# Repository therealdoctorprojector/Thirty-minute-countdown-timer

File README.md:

Thirty minute countdown timer.

If you have ever needed to know when half an hour has passed, this project is for you.
When you turn this device on it will:
Start a countdown timer for 30 minutes.
Show the time remaining.
After 30 minutes a speaker will make a continuous sound until you turn the device off.

The files provided should give you everything you need to make your own timer.
Note that some skill and knowledge are required to make this.

Files:
1. Software source code.
2. Bill Of Materials.
3. PCB design files.

General notes on the software:
1. The software was developed and tested using the Arduino IDE.
2. The thirty minutes has been hard-coded in the software, but you are welcome to change that number and re-compile the software.
3. You can add extra features to the software as you see fit.

General notes on the Bill Of Materials:
1. Prices on the parts are estimates only.
2. There are many variants on the OLED display, in terms of pin count, pin assignments and variations in the size and hole spacing.
3. The switch must be a mechanical latching type.

General notes on the PCB:
1. All through-hole components for ease of soldering.
2. AA batteries are the preferred power source. With some minor adjustments you could use a CR123 lithium battery, or a CR2032 lithium coin cell. You are encouraged to change the PCB design to accommodate the relevant battery holders.
3. The AA battery holder is a widely-copied design “Keystone 2462”, this should give you the correct pin-spacing to fit.
4. I don’t recommend it but you can solder the display board to the main PCB.
5. You are welcome to substitute a surface mount ATTiny85 by making the relevant changes to the PCB. I may generate a revision of the PCB which can be populated with either the 8 pin DIP or the 8-SOIC version.
6. An ICSP header is included on the PCB. No need to fit a 3x2 pin header if you use the Sparkfun PoGo adapter.
7. M3 clearance holes in each corner for fitting the PCB in an enclosure. I would encourage 3D printer users to share a simple design for a suitable case.
8. M2 clearance holes provided to support the OLED display.

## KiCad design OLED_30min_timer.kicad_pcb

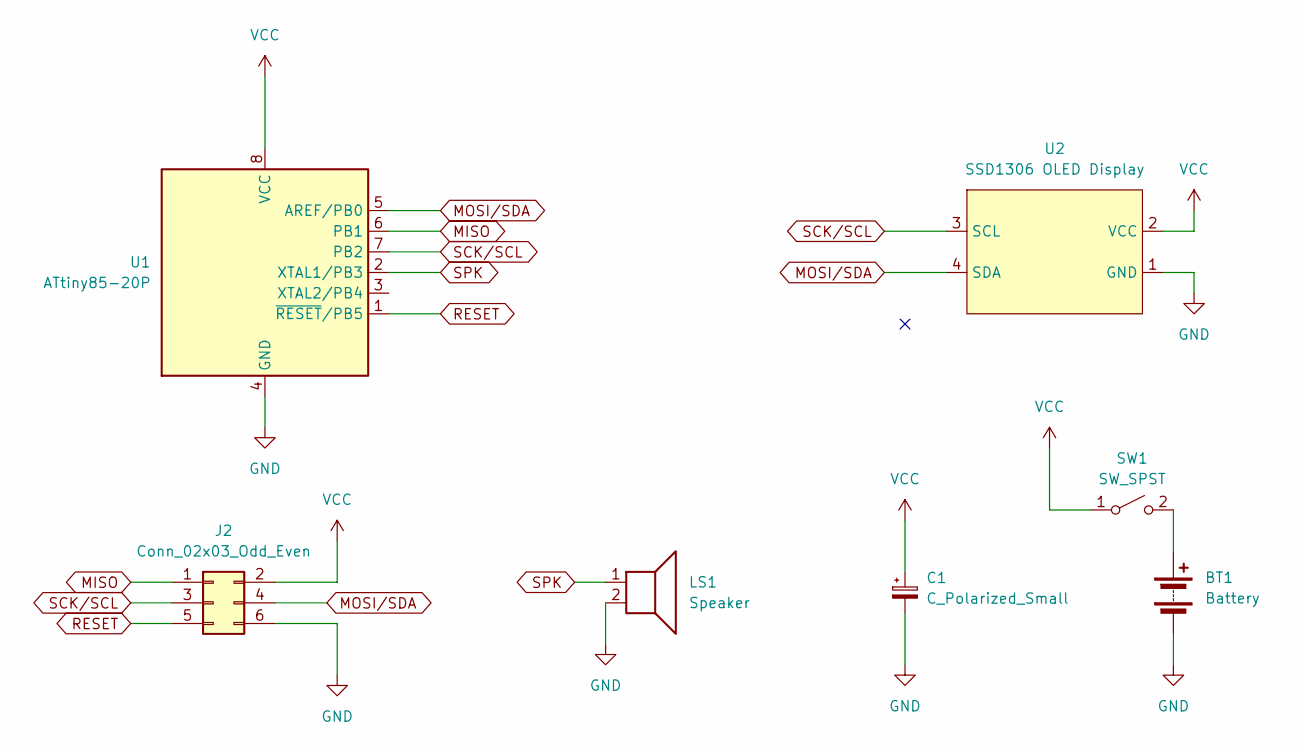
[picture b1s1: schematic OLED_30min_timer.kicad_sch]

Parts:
BT1: Battery; BatteryHolder_Keystone_2462_2xAA
C1: C_Polarized_Small; CP_Radial_D5.0mm_P2.50mm
J2: Conn_02x03_Odd_Even; PinHeader_2x03_P2.54mm_Vertical
LS1: Speaker; Buzzer_12x9.5RM7.6
SW1: SW_SPST; SW_KAN-15_PHT
U1: ATtiny85-20P; DIP-8_W7.62mm
U2: SSD1306 OLED Display; SSD1306_OLED_Display_1x04_P2.54mm

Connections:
GND: BT1.2 (-), C1.2, J2.6, LS1.2, U1.4 (GND), U2.1 (GND)
MISO: J2.1, U1.6 (PB1)
MOSI/SDA: J2.4, U1.5 (AREF/PB0), U2.4 (SDA)
unnamed: BT1.1 (+), SW1.2 (B)
RESET: J2.5, U1.1 (~RESET/PB5)
SCK/SCL: J2.3, U1.7 (PB2), U2.3 (SCL)
SPK: LS1.1, U1.2 (XTAL1/PB3)
VCC: C1.1, J2.2, SW1.1 (A), U1.8 (VCC), U2.2 (VCC)

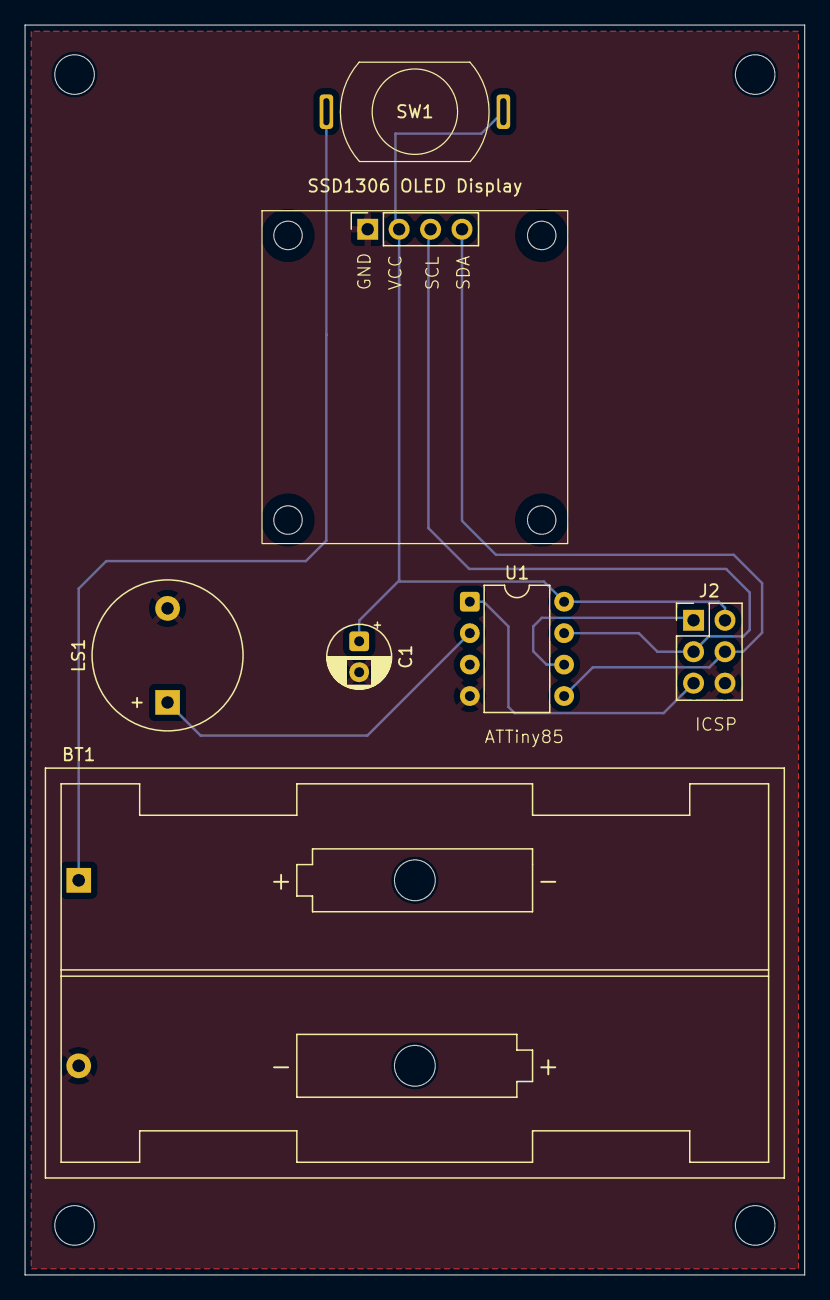
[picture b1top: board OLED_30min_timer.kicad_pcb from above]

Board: 2 copper layers, 63.0 x 101.0 mm, 7 parts (0 on the bottom side), 8 nets.

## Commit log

2026-03-17 Add files via upload
    KiCAD footprint and symbol for the OLED display.
2026-03-17 Add files via upload
    Compiles in the Arduino IDE.
    Don't forget to specify your target as ATTiny85, board type "Bare ATtiny85, 1MHz internal oscillator" and programmer as "ICSP via USB".
